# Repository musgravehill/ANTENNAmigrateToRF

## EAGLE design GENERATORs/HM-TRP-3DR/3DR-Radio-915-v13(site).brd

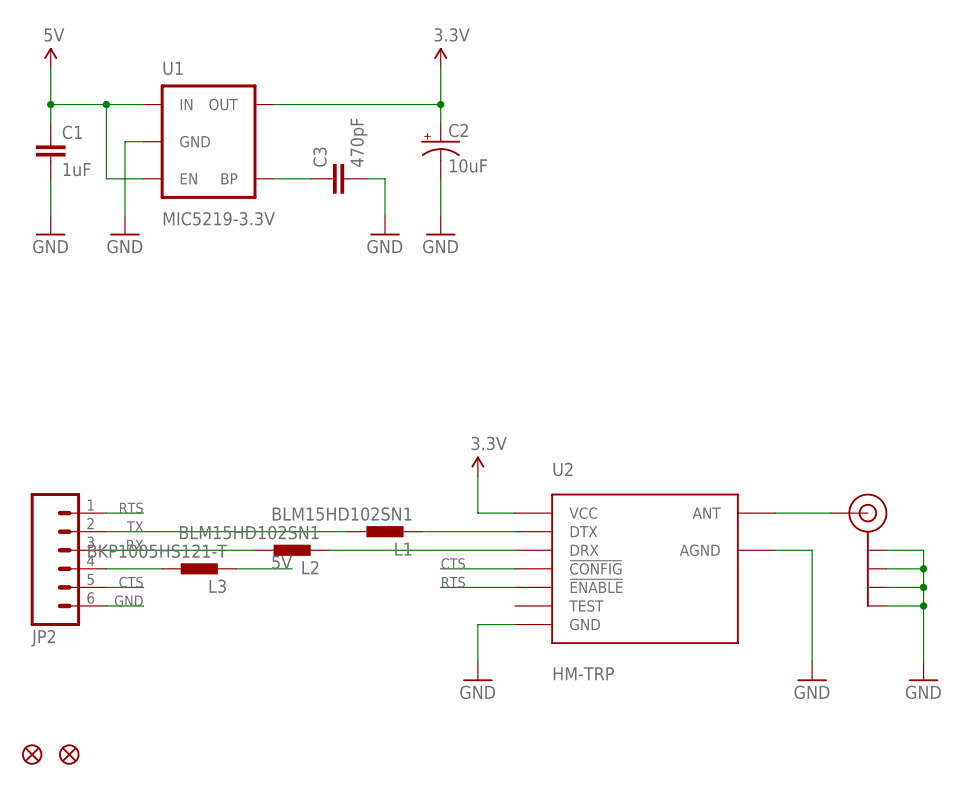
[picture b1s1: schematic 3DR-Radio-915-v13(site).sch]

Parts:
C1: 1uF; 0402-CAP
C2: 10uF; EIA3216
C3: 470pF; 0402-CAP
J$2: SMA_EDGE; SMA-EDGE
JP1, JP3: FIDUCIAL1X2; FIDUCIAL-1X2
JP2: M06SIP; 1X06
L1, L2: BLM15HD102SN1; 0402-IND
L3: BKP1005HS121-T; 0402-IND
U1: MIC5219-3.3V; SOT23-5
U2: HM-TRP; HM-TRP-SMD

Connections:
3.3V: C2.A (+), U1.5 (OUT), U2.VCC
5V: C1.1, L3.P$2 (2), U1.1 (IN), U1.3 (EN)
CTS: JP2.5, U2.!CONFIG
GND: C1.2, C2.C (-), C3.2, J$2.GND@0 (GND), J$2.GND@1 (GND), J$2.GND@2 (GND), J$2.GND@3 (GND), JP2.6, U1.2 (GND), U2.AGND, U2.GND
unnamed: L1.P$2 (2), U2.DTX
unnamed: L2.P$2 (2), U2.DRX
unnamed: JP2.4, L3.P$1 (1)
unnamed: J$2.SIG (SIGNAL), U2.ANT
unnamed: C3.1, U1.4 (BP)
RTS: JP2.1, U2.!ENABLE
RX: JP2.3, L2.P$1 (1)
TX: JP2.2, L1.P$1 (1)

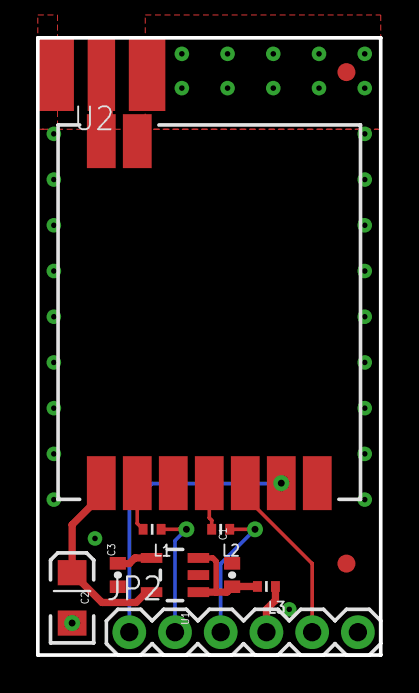
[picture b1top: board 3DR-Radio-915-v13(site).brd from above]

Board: 2 copper layers, 19.1 x 34.3 mm, 12 parts (0 on the bottom side), 12 nets.

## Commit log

2018-03-05 :tada: Added .gitattributes
2018-03-05 iinit
2018-03-06 info
2018-03-06 howto
2018-03-06 note
2018-03-07 dummy
2018-03-07 oversampling opamp
2018-03-07 helix
2018-03-08 directiv coupler
2018-03-11 soft
2018-03-11 MACOM coupler SMD
2018-03-12 coupler
2018-03-18 detector
2018-03-18 detedetec
2018-03-19 detec
2018-03-19 detect
2018-03-19 detectorr
2018-03-20 v2 det
